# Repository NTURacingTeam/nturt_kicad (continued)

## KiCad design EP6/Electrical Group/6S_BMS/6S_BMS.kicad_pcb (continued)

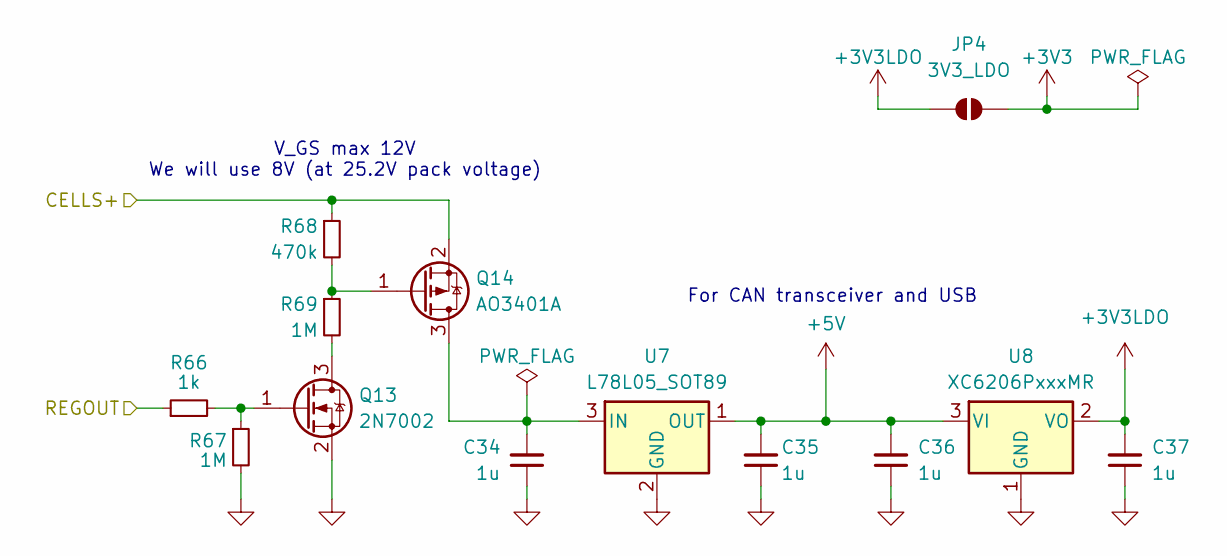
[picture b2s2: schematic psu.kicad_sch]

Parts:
C34, C35, C36, C37: 1u; C_0402_1005Metric
JP4: 3V3_LDO; SolderJumper-2_P1.3mm_Open_TrianglePad1.0x1.5mm
Q13: 2N7002; SOT-23
Q14: AO3401A; SOT-23
R66: 1k; R_0402_1005Metric
R67, R69: 1M; R_0402_1005Metric
R68: 470k; R_0402_1005Metric
U7: L78L05_SOT89; SOT-89-3
U8: XC6206PxxxMR; SOT-23-3

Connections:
+3V3: JP4.1 (A); also elsewhere on the board
+3V3LDO: C37.2, JP4.2 (B), U8.2 (VO)
+5V: C35.2, C36.2, U7.1 (OUT), U8.3 (VI); also elsewhere on the board
/CELLS+: Q14.2 (S), R68.1; also elsewhere on the board
/REGOUT: R66.1; also elsewhere on the board
GND: C34.1, C35.1, C36.1, C37.1, Q13.2 (S), R67.2, U7.2 (GND), U8.1 (GND); also elsewhere on the board
unnamed: Q13.3 (D), R69.2
unnamed: Q13.1 (G), R66.2, R67.1
unnamed: C34.2, Q14.3 (D), U7.3 (IN)
unnamed: Q14.1 (G), R68.2, R69.1

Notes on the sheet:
For CAN transceiver and USB
V_GS max 12V We will use 8V (at 25.2V pack voltage)

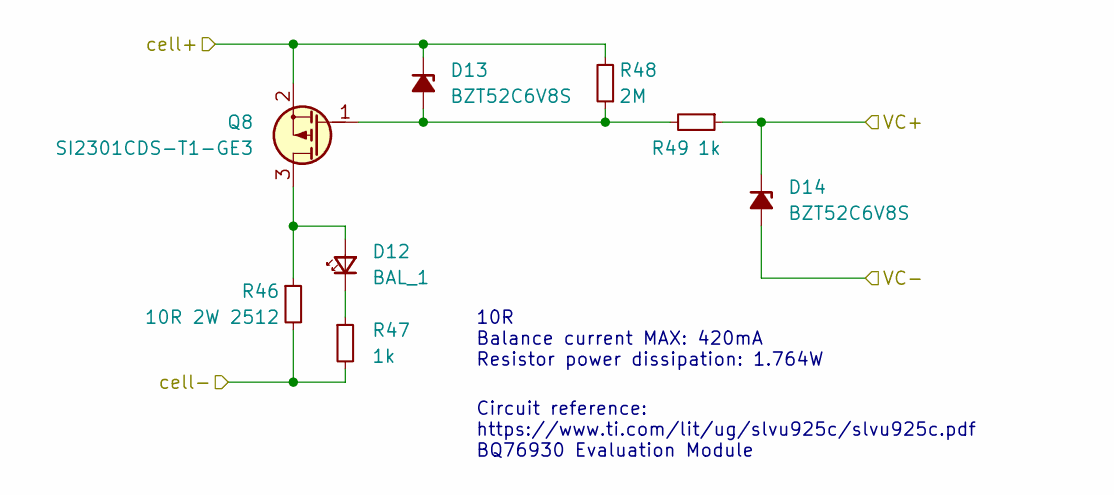
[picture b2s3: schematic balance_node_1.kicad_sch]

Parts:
D12: BAL_1; LED_0603_1608Metric
D13, D14: BZT52C6V8S; D_SOD-323
Q8: SI2301CDS-T1-GE3; SOT-23
R46: 10R 2W 2512; R_2512_6332Metric
R47, R49: 1k; R_0402_1005Metric
R48: 2M; R_0402_1005Metric

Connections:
/Balance Node 1/cell-: D13.1 (K), Q8.2 (S), R48.2; also elsewhere on the board
/C4: D14.2 (A); also elsewhere on the board
/C5: D14.1 (K), R49.1; also elsewhere on the board
unnamed: D12.1 (K), R47.1
unnamed: D13.2 (A), Q8.1 (G), R48.1, R49.2

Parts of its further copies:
D9, D15, D18, D21, D24: BAL_1; LED_0603_1608Metric
D10, D11, D16, D17, D19, D20, D22, D23, D25, D26: BZT52C6V8S; D_SOD-323
Q7, Q9, Q10, Q11, Q12: SI2301CDS-T1-GE3; SOT-23
R42, R50, R54, R58, R62: 10R 2W 2512; R_2512_6332Metric
R43, R51, R53, R55, R57, R59, R61, R63, R65: 1k; R_0402_1005Metric
R44, R52, R56, R60, R64: 2M; R_0402_1005Metric

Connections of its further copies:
/Balance Node 1/cell+: D10.1 (K), Q7.2 (S), R44.2; also elsewhere on the board
/Balance Node 1/cell-: R42.2, R43.2; also elsewhere on the board
/Balance Node 4/cell-: D22.1 (K), Q11.2 (S), R54.2, R55.2, R60.2; also elsewhere on the board
/Balance Node 5/cell-: D25.1 (K), Q12.2 (S), R58.2, R59.2, R64.2; also elsewhere on the board
/C0: D26.2 (A); also elsewhere on the board
/C1: D23.2 (A), D26.1 (K), R65.1; also elsewhere on the board
/C2: D20.2 (A), D23.1 (K), R61.1; also elsewhere on the board
/C3: D20.1 (K), R57.1; also elsewhere on the board
/C3.5: D17.2 (A); also elsewhere on the board
/C4: D17.1 (K), R53.1; also elsewhere on the board
/C5: D11.2 (A); also elsewhere on the board
/CT3: D19.1 (K), Q10.2 (S), R50.2, R51.2, R56.2; also elsewhere on the board
CELL-: R62.2, R63.2; also elsewhere on the board
unnamed: D9.2 (A), Q7.3 (D), R42.1
unnamed: D9.1 (K), R43.1
unnamed: D15.2 (A), Q9.3 (D), R50.1
unnamed: D15.1 (K), R51.1
unnamed: D16.2 (A), Q9.1 (G), R52.1, R53.2
unnamed: D18.2 (A), Q10.3 (D), R54.1
unnamed: D18.1 (K), R55.1
unnamed: D19.2 (A), Q10.1 (G), R56.1, R57.2
unnamed: D21.2 (A), Q11.3 (D), R58.1
unnamed: D21.1 (K), R59.1
unnamed: D22.2 (A), Q11.1 (G), R60.1, R61.2
unnamed: D24.2 (A), Q12.3 (D), R62.1
unnamed: D24.1 (K), R63.1
unnamed: D25.2 (A), Q12.1 (G), R64.1, R65.2

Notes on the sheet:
10R Balance current MAX: 420mA Resistor power dissipation: 1.764W
Circuit reference: https://www.ti.com/lit/ug/slvu925c/slvu925c.pdf BQ76930 Evaluation Module

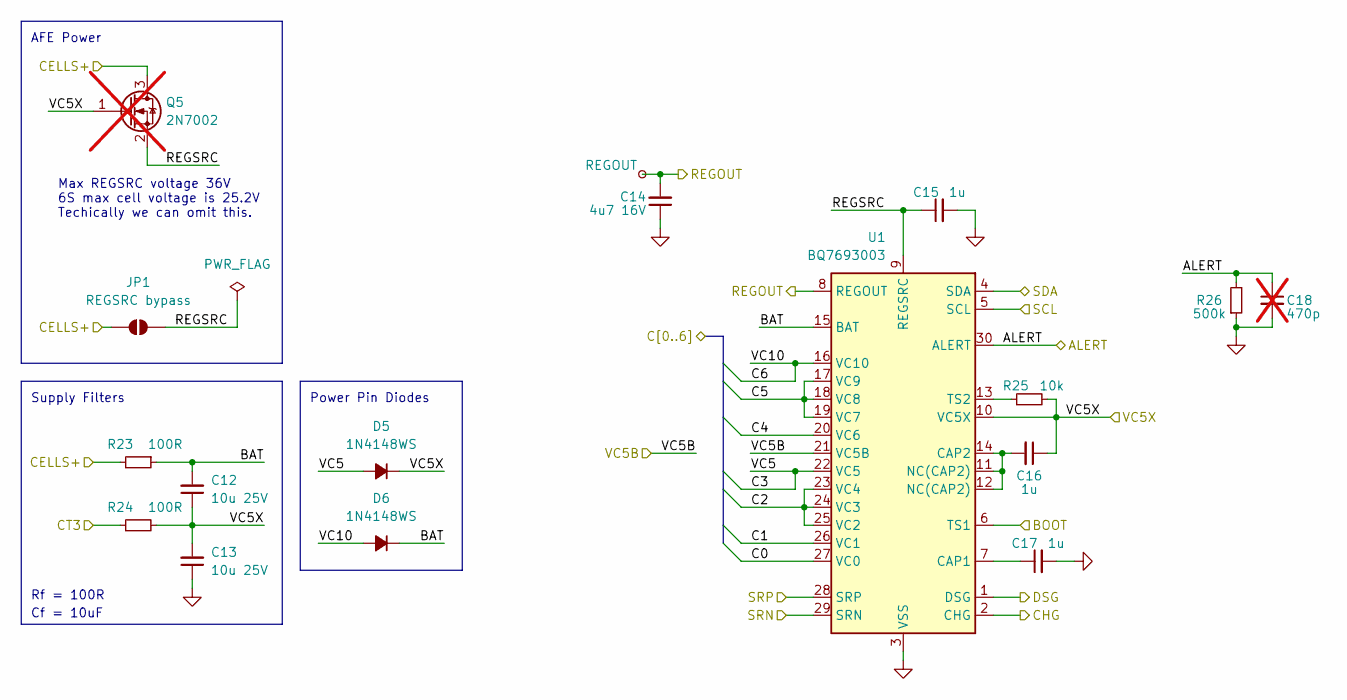
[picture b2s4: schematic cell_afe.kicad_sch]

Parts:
C12, C13: 10u 25V; C_0805_2012Metric
C14: 4u7 16V; C_0603_1608Metric
C15: 1u; C_0603_1608Metric
C16, C17: 1u; C_0402_1005Metric
C18: 470p; C_0402_1005Metric; not fitted
D5, D6: 1N4148WS; D_SOD-323
JP1: REGSRC bypass; SolderJumper-2_P1.3mm_Open_TrianglePad1.0x1.5mm
Q5: 2N7002; SOT-23; not fitted
R23, R24: 100R; R_0402_1005Metric
R25: 10k; R_0402_1005Metric
R26: 500k; R_0402_1005Metric
TP12: REGOUT; TestPoint_Pad_D1.0mm
U1: BQ7693003; TSSOP-30_4.4x7.8mm_P0.5mm

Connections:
/AFE/BAT: C12.2, D6.1 (K), R23.1, U1.15 (BAT)
/AFE/REGSRC: C15.1, JP1.1 (A), Q5.2 (S), U1.9 (REGSRC)
/ALERT: C18.1, R26.2, U1.30 (ALERT); also elsewhere on the board
/C0: U1.27 (VC0); also elsewhere on the board
/C1: U1.26 (VC1); also elsewhere on the board
/C2: U1.23 (VC4), U1.24 (VC3), U1.25 (VC2); also elsewhere on the board
/C3: D5.2 (A), U1.22 (VC5); also elsewhere on the board
/C3.5: U1.21 (VC5B); also elsewhere on the board
/C4: U1.20 (VC6); also elsewhere on the board
/C5: U1.17 (VC9), U1.18 (VC8), U1.19 (VC7); also elsewhere on the board
/CELLS+: JP1.2 (B), Q5.3 (D), R23.2; also elsewhere on the board
/CHG_EN: U1.2 (CHG); also elsewhere on the board
/CT3: R24.1; also elsewhere on the board
/DSC_EN: U1.1 (DSG); also elsewhere on the board
/MODE_CTL: U1.6 (TS1); also elsewhere on the board
/REGOUT: C14.2, TP12.1, U1.8 (REGOUT); also elsewhere on the board
/SCL: U1.5 (SCL); also elsewhere on the board
/SDA: U1.4 (SDA); also elsewhere on the board
/SRN: U1.29 (SRN); also elsewhere on the board
/SRP: U1.28 (SRP); also elsewhere on the board
/VC5X: C12.1, C13.2, C16.1, D5.1 (K), Q5.1 (G), R24.2, R25.2, U1.10 (VC5X); also elsewhere on the board
GND: C13.1, C14.1, C15.2, C17.2, C18.2, R26.1, U1.3 (VSS); also elsewhere on the board
unnamed: C17.1, U1.7 (CAP1)
unnamed: C16.2, U1.11 (NC(CAP2)), U1.12 (NC(CAP2)), U1.14 (CAP2)
unnamed: R25.1, U1.13 (TS2)

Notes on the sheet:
Max REGSRC voltage 36V 6S max cell voltage is 25.2V Techically we can omit this.
AFE Power
Cf = 10uF
Power Pin Diodes
Supply Filters
Rf = 100R

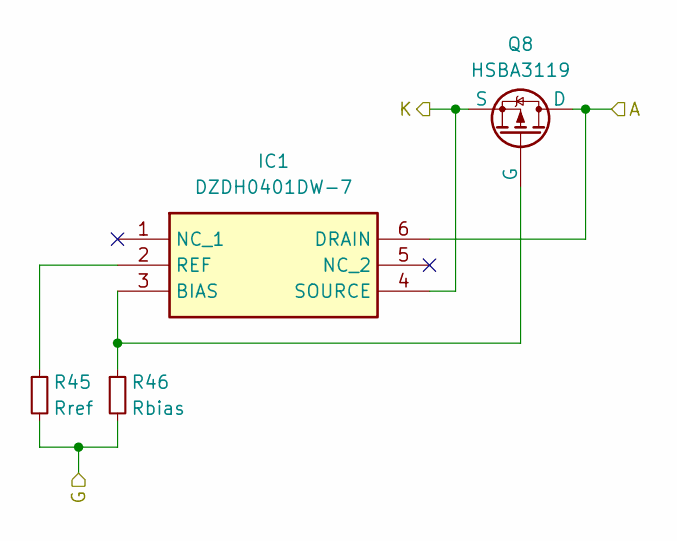
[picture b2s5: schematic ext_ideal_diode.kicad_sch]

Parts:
IC1: DZDH0401DW-7; SOT65P210X110-6N; Mouser Part Number 621-DZDH0401DW-7
Q8: HSBA3119; HSBA3119_PRPAK5X6
R45: Rref; R_0402_1005Metric
R46: Rbias; R_0402_1005Metric

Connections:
/EXT Ideal Diode/A: IC1.6 (DRAIN), Q8.D; also elsewhere on the board
/PACK+: IC1.4 (SOURCE), Q8.S; also elsewhere on the board

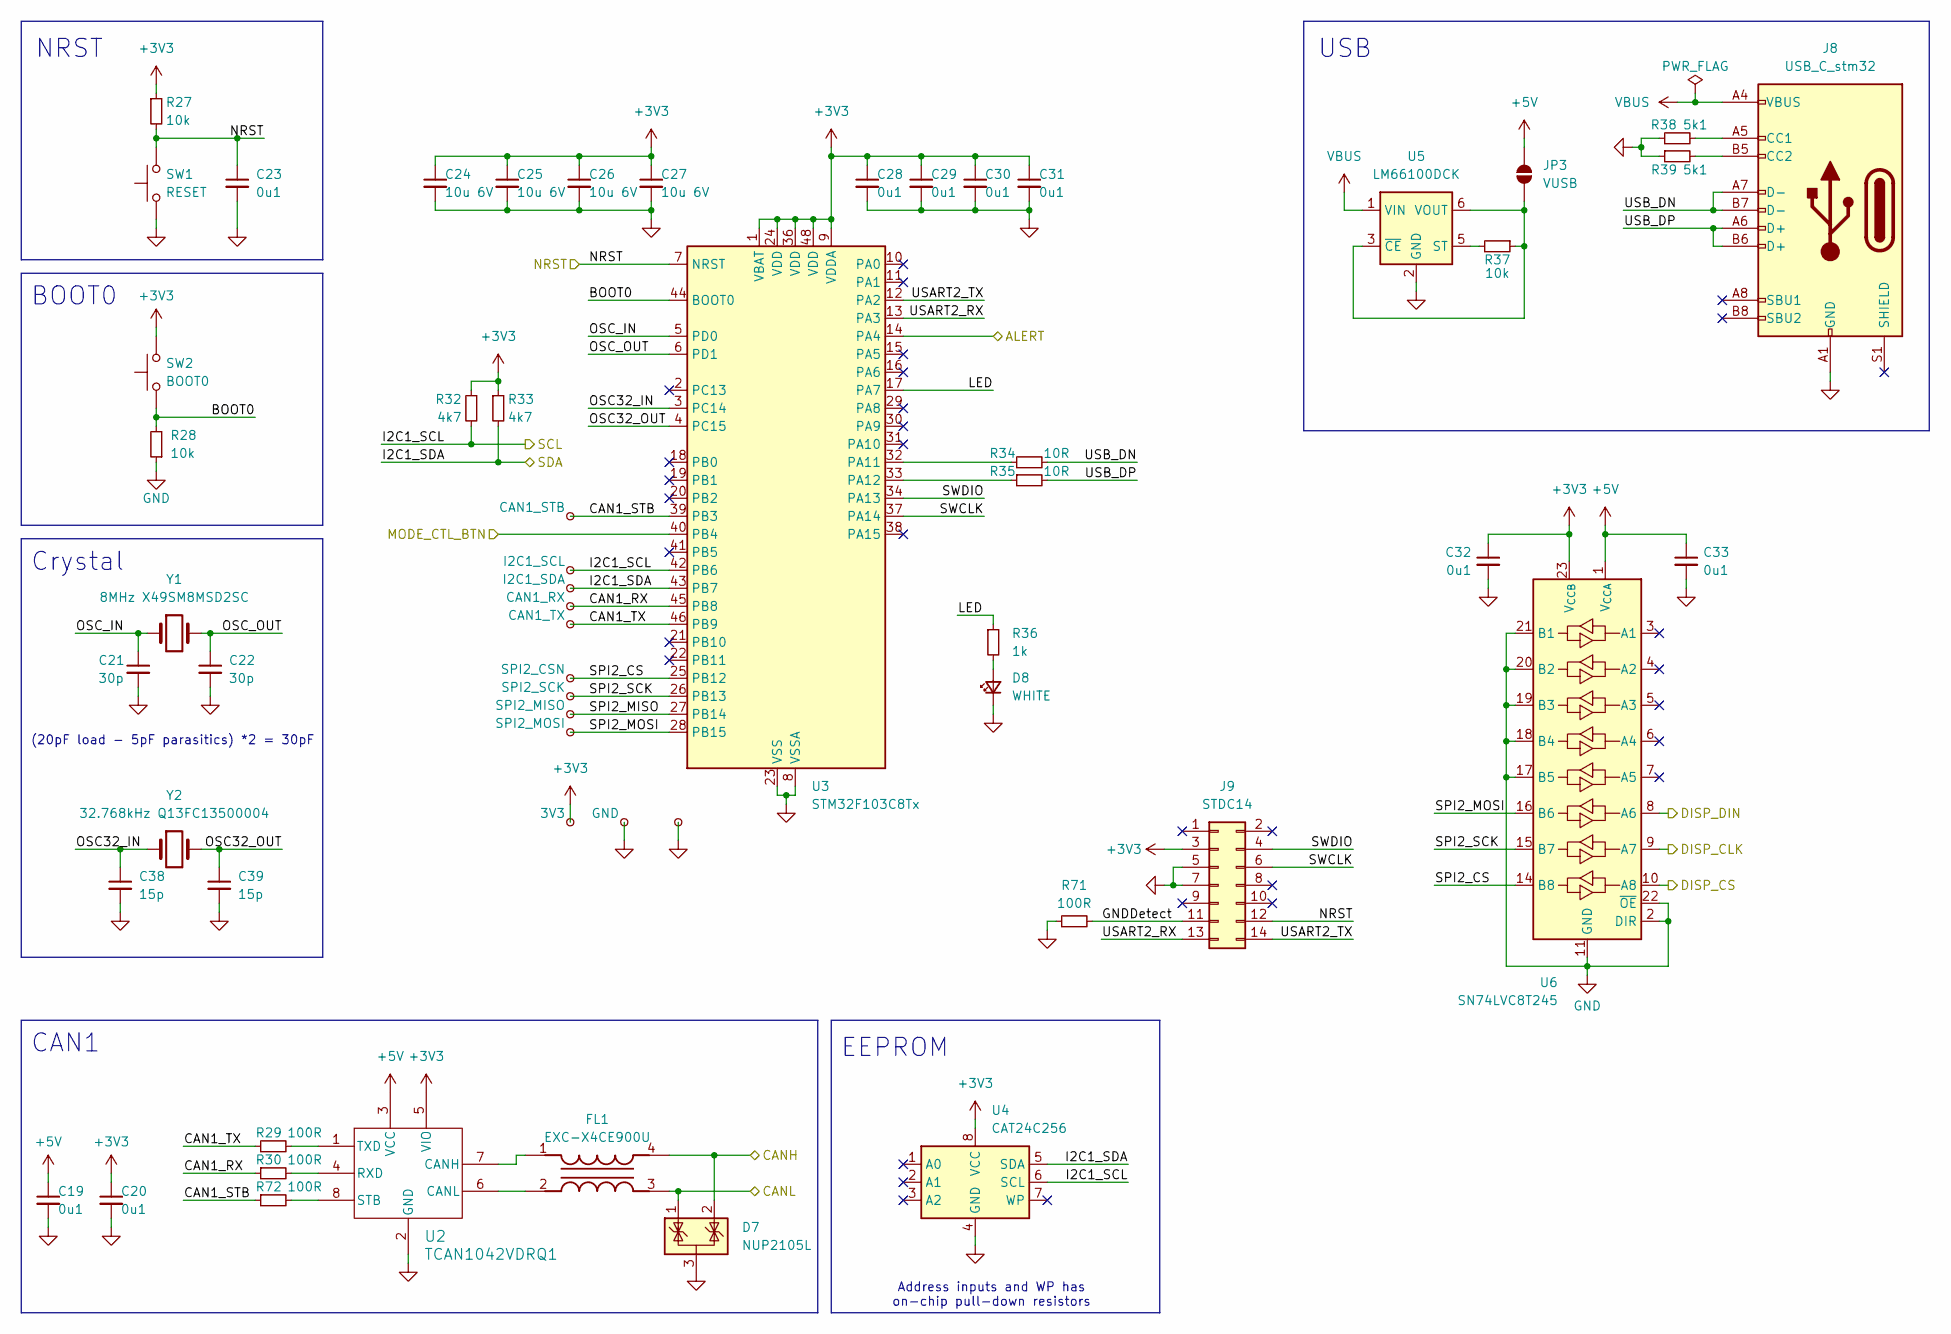
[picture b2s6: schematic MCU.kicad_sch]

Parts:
C19, C20, C23, C28, C29, C30, C31, C32, C33: 0u1; C_0402_1005Metric
C21, C22: 30p; C_0402_1005Metric
C24, C25, C26, C27: 10u 6V; C_0402_1005Metric
C38, C39: 15p; C_0402_1005Metric
D7: NUP2105L; SOT-23
D8: WHITE; LED_0603_1608Metric
FL1: EXC-X4CE900U; EXCX4CE900U; Mouser Part Number 667-EXC-X4CE900U
J8: USB_C_stm32; USB_C_Receptacle_GCT_USB4105-xx-A_16P_TopMnt_Horizontal
J9: STDC14; box_header_14P_pitch127
JP3: VUSB; SolderJumper-2_P1.3mm_Open_TrianglePad1.0x1.5mm
R27, R28, R37: 10k; R_0402_1005Metric
R29, R30, R72: 100R; R_0402_1005Metric
R32, R33: 4k7; R_0402_1005Metric
R34, R35: 10R; R_0402_1005Metric
R36: 1k; R_0603_1608Metric
R38, R39: 5k1; R_0402_1005Metric
R71: 100R; R_0603_1608Metric
SW1: RESET; SW_Tactile_SPST_NO_Straight_CK_PTS636Sx25SMTRLFS
SW2: BOOT0; SW_Tactile_SPST_NO_Straight_CK_PTS636Sx25SMTRLFS
TP1: I2C1_SCL; TestPoint_Pad_D1.0mm
TP2: I2C1_SDA; TestPoint_Pad_D1.0mm
TP3: CAN1_RX; TestPoint_Pad_D1.0mm
TP4: CAN1_TX; TestPoint_Pad_D1.0mm
TP5: CAN1_STB; TestPoint_Pad_D1.0mm
TP6: SPI2_CSN; TestPoint_Pad_D1.0mm
TP7: SPI2_SCK; TestPoint_Pad_D1.0mm
TP8: SPI2_MISO; TestPoint_Pad_D1.0mm
TP9: SPI2_MOSI; TestPoint_Pad_D1.0mm
TP10: 3V3; TestPoint_Pad_D1.0mm
TP11, TP14: GND; TestPoint_Pad_D1.0mm
U2: TCAN1042VDRQ1; SOIC-8_3.9x4.9mm_P1.27mm
U3: STM32F103C8Tx; LQFP-48_7x7mm_P0.5mm
U4: CAT24C256; SOIC-8_3.9x4.9mm_P1.27mm
U5: LM66100DCK; SOT-363_SC-70-6
U6: SN74LVC8T245; TSSOP-24_4.4x7.8mm_P0.65mm
Y1: 8MHz X49SM8MSD2SC; Crystal_SMD_5032-2Pin_5.0x3.2mm
Y2: 32.768kHz Q13FC13500004; Crystal_SMD_3215-2Pin_3.2x1.5mm

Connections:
+3V3: C20.1, C24.1, C25.1, C26.1, C27.1, C28.1, C29.1, C30.1, C31.1, C32.1, J9.3, R27.1, R32.1, R33.1, SW2.2, TP10.1, U2.5 (VIO), U3.1 (VBAT), U3.9 (VDDA), U3.24 (VDD), U3.36 (VDD), U3.48 (VDD), U4.8 (VCC), U6.23 (V_{CCB}), U6.24 (V_{CCB}); also elsewhere on the board
+5V: C19.1, C33.1, JP3.2 (B), U2.3 (VCC), U6.1 (V_{CCA}); also elsewhere on the board
/ALERT: U3.14 (PA4); also elsewhere on the board
/CANH: D7.2 (K), FL1.4; also elsewhere on the board
/CANL: D7.1 (K), FL1.3; also elsewhere on the board
/DISP_CLK: U6.9 (A7); also elsewhere on the board
/DISP_CS: U6.10 (A8); also elsewhere on the board
/DISP_DIN: U6.8 (A6); also elsewhere on the board
/MCU/BOOT0: R28.2, SW2.1, U3.44 (BOOT0)
/MCU/CAN1_RX: R30.1, TP3.1, U3.45 (PB8)
/MCU/CAN1_STB: R72.1, TP5.1, U3.39 (PB3)
/MCU/CAN1_TX: R29.1, TP4.1, U3.46 (PB9)
/MCU/GNDDetect: J9.11, R71.2
/MCU/LED: R36.1, U3.17 (PA7)
/MCU/OSC32_IN: C38.1, U3.3 (PC14), Y2.1
/MCU/OSC32_OUT: C39.1, U3.4 (PC15), Y2.2
/MCU/OSC_IN: C21.1, U3.5 (PD0), Y1.1
/MCU/OSC_OUT: C22.1, U3.6 (PD1), Y1.2
/MCU/SPI2_CS: TP6.1, U3.25 (PB12), U6.14 (B8)
/MCU/SPI2_MISO: TP8.1, U3.27 (PB14)
/MCU/SPI2_MOSI: TP9.1, U3.28 (PB15), U6.16 (B6)
/MCU/SPI2_SCK: TP7.1, U3.26 (PB13), U6.15 (B7)
/MCU/SWCLK: J9.6, U3.37 (PA14)
/MCU/SWDIO: J9.4, U3.34 (PA13)
/MCU/USART2_RX: J9.13, U3.13 (PA3)
/MCU/USART2_TX: J9.14, U3.12 (PA2)
/MCU/USB_DN: J8.A7 (D-), J8.B7 (D-), R34.2
/MCU/USB_DP: J8.A6 (D+), J8.B6 (D+), R35.2
/MCU_RST: C23.1, J9.12, R27.2, SW1.2, U3.7 (NRST); also elsewhere on the board
/MODE_CTL: U3.40 (PB4); also elsewhere on the board
/SCL: R32.2, TP1.1, U3.42 (PB6), U4.6 (SCL); also elsewhere on the board
/SDA: R33.2, TP2.1, U3.43 (PB7), U4.5 (SDA); also elsewhere on the board
GND: C19.2, C20.2, C21.2, C22.2, C23.2, C24.2, C25.2, C26.2, C27.2, C28.2, C29.2, C30.2, C31.2, C32.2, C33.2, C38.2, C39.2, D7.3 (A), D8.1 (K), J8.A1 (GND), J8.A12 (GND), J8.B1 (GND), J8.B12 (GND), J9.5, J9.7, R28.1, R38.1, R39.1, R71.1, SW1.1, TP11.1, TP14.1, U2.2 (GND), U3.8 (VSSA), U3.23 (VSS), U3.35 (VSS), U3.47 (VSS), U4.4 (GND), U5.2 (GND), U6.2 (DIR), U6.11 (GND), U6.12 (GND), U6.13 (GND), U6.17 (B5), U6.18 (B4), U6.19 (B3), U6.20 (B2), U6.21 (B1), U6.22 (~OE); also elsewhere on the board
unnamed: D8.2 (A), R36.2
unnamed: J8.A5 (CC1), R38.2
unnamed: J8.B5 (CC2), R39.2
unnamed: JP3.1 (A), R37.1, U5.3 (~CE), U5.6 (VOUT)
unnamed: FL1.1, U2.7 (CANH)
unnamed: FL1.2, U2.6 (CANL)
unnamed: R30.2, U2.4 (RXD)
unnamed: R72.2, U2.8 (STB)
unnamed: R29.2, U2.1 (TXD)
unnamed: R34.1, U3.32 (PA11)
unnamed: R35.1, U3.33 (PA12)
unnamed: R37.2, U5.5 (ST)
VBUS: J8.A4 (VBUS), J8.A9 (VBUS), J8.B4 (VBUS), J8.B9 (VBUS), U5.1 (VIN)

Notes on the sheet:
Address inputs and WP has on-chip pull-down resistors
BOOT0
CAN1
(20pF load - 5pF parasitics) *2 = 30pF
USB
NRST
Crystal
EEPROM

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
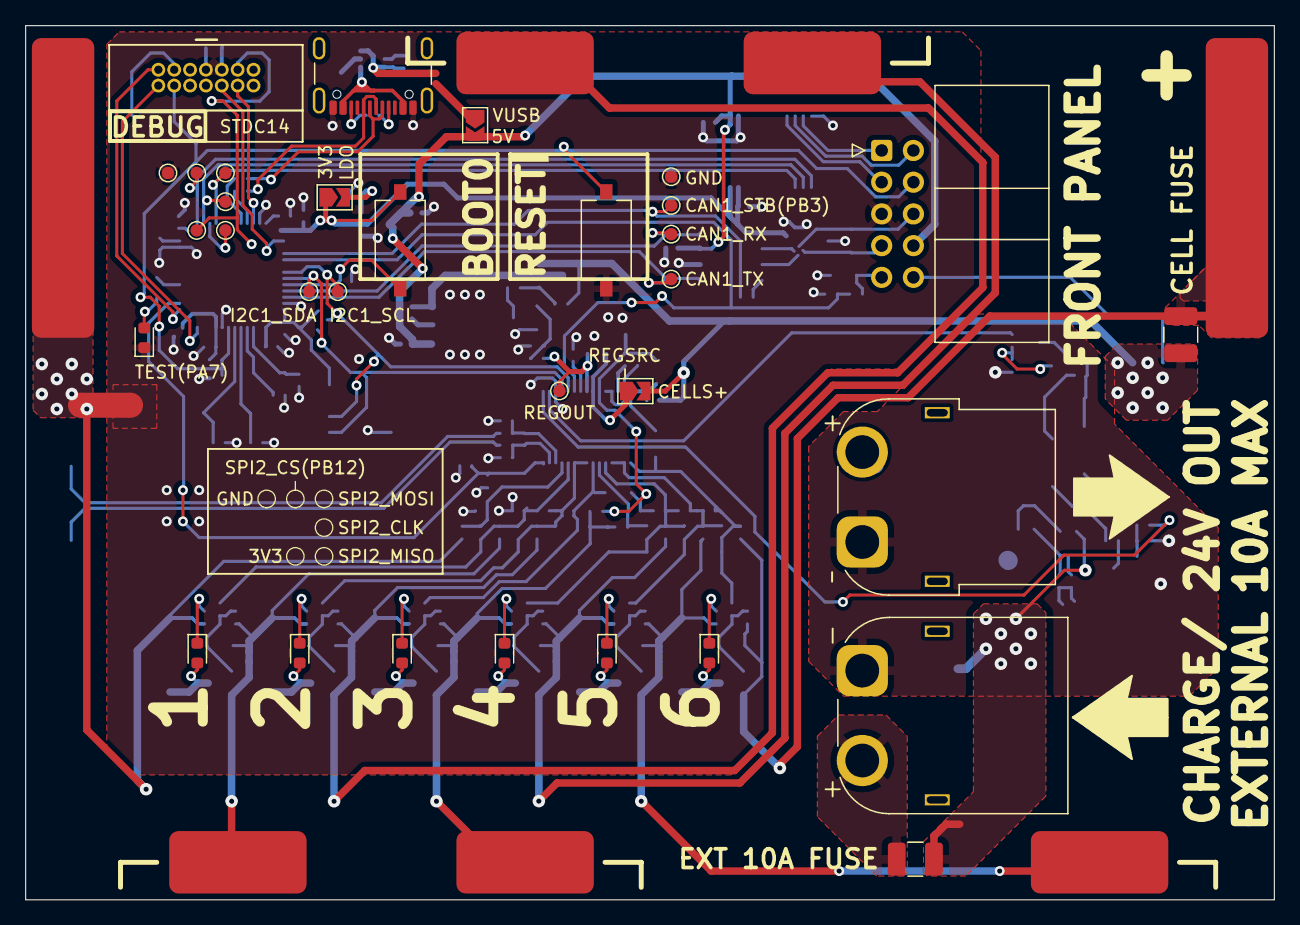
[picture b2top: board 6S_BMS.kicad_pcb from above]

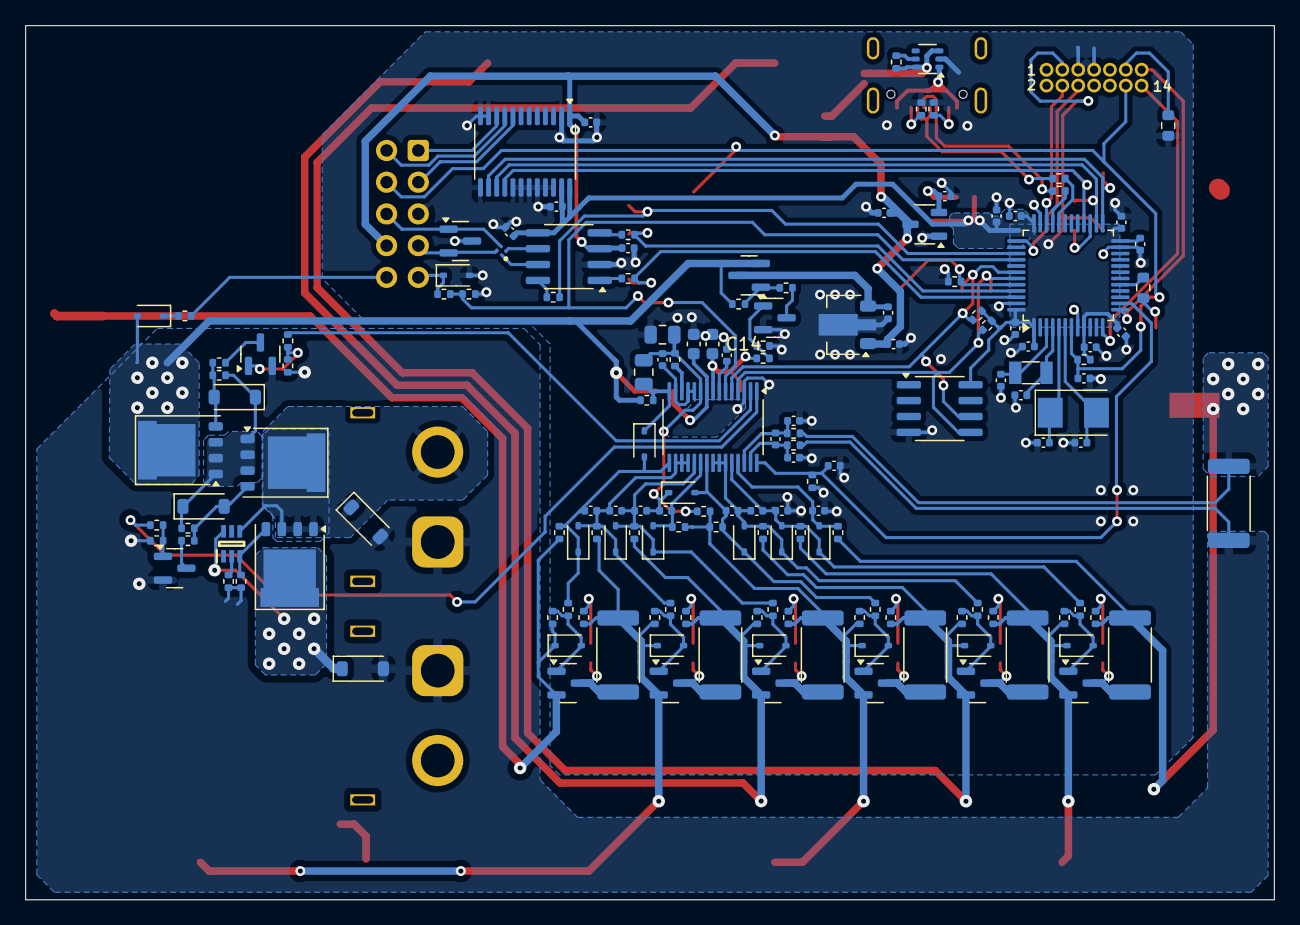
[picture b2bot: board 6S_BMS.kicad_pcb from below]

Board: 2 copper layers, 100.0 x 70.0 mm, 189 parts (155 on the bottom side), 112 nets.

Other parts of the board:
NT1: NetTie_2; NetTie-2_SMD_Pad2.0mm
Q6: HSBA3119; HSBA3119_PRPAK5X6
R40: Rref; R_0402_1005Metric
R41: Rbias; R_0402_1005Metric

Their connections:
/EXT Ideal Diode/A: Q6.D; also elsewhere on the board
/PACK+: Q6.S; also elsewhere on the board
/PACK-: R40.2, R41.2; also elsewhere on the board
CELL-: NT1.2; also elsewhere on the board
GND: NT1.1; also elsewhere on the board

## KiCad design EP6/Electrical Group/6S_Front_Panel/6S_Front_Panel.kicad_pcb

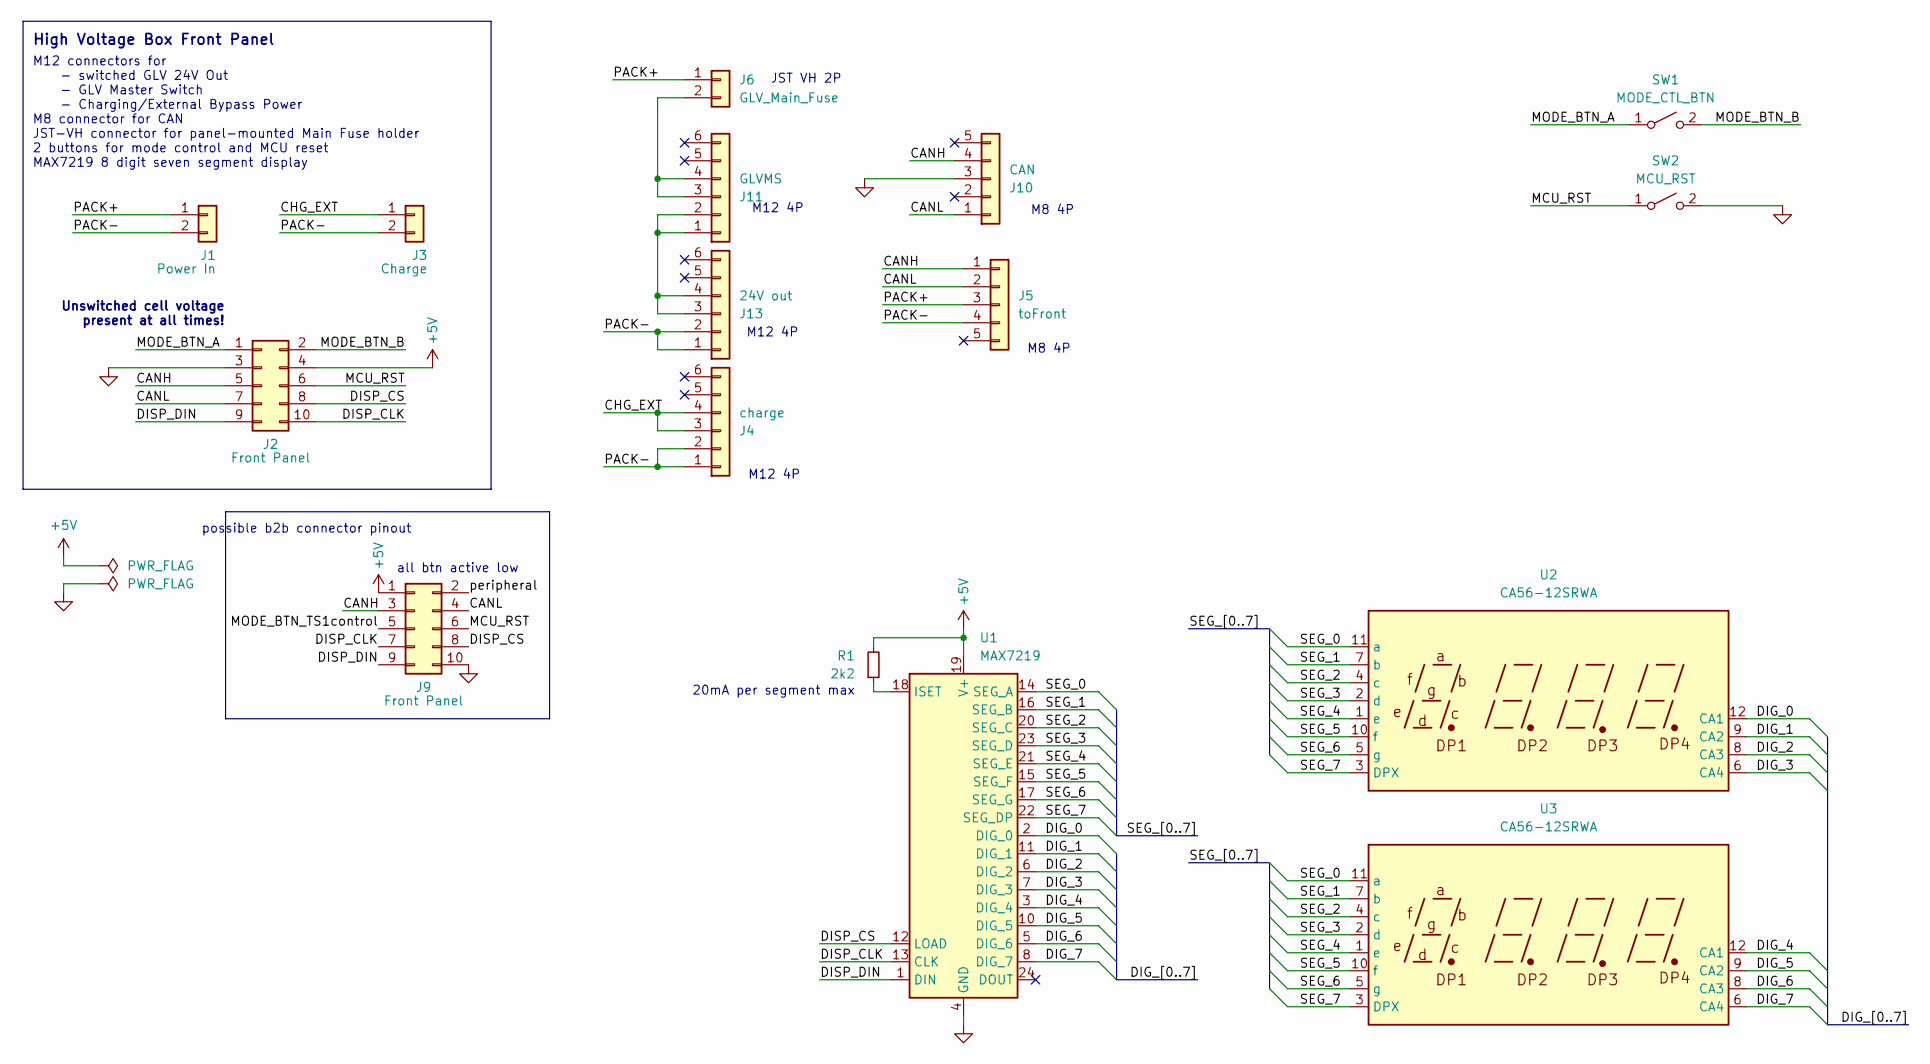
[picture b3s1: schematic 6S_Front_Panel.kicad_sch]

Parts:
J1: Power In; AMASS_XT60PW-M_1x02_P7.20mm_Horizontal
J2, J9: Front Panel; IDC-Header_2x05_P2.54mm_Horizontal
J3: Charge; AMASS_XT60PW-F_1x02_P7.20mm_Horizontal
J4: charge; M12-5P-ground; Part Number 1-0601FBV0T
J5: toFront; WP-04F3-26-11
J6: GLV_Main_Fuse; JST_VH_B2PS-VH_1x02_P3.96mm_Horizontal
J10: CAN; WP-04F3-26-11
J11: GLVMS; M12-5P-ground; Part Number 1-0601FBV0T
J13: 24V out; M12-5P-ground; Part Number 1-0601FBV0T
R1: 2k2; R_0402_1005Metric_Pad0.72x0.64mm_HandSolder
SW1: MODE_CTL_BTN; PinHeader_1x02_P2.54mm_Vertical
SW2: MCU_RST; PinHeader_1x02_P2.54mm_Vertical
U1: MAX7219; SOIC-24W_7.5x15.4mm_P1.27mm
U2, U3: CA56-12SRWA; CA56-12EWA

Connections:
+5V: J2.4, J9.1, R1.2, U1.19 (V+)
/CANH: J2.5, J5.1, J9.3, J10.4
/CANL: J2.7, J5.2, J9.4, J10.1
/CHG_EXT: J3.1, J4.3, J4.4
/DIG_0: U1.2 (DIG_0), U2.12 (CA1)
/DIG_1: U1.11 (DIG_1), U2.9 (CA2)
/DIG_2: U1.6 (DIG_2), U2.8 (CA3)
/DIG_3: U1.7 (DIG_3), U2.6 (CA4)
/DIG_4: U1.3 (DIG_4), U3.12 (CA1)
/DIG_5: U1.10 (DIG_5), U3.9 (CA2)
/DIG_6: U1.5 (DIG_6), U3.8 (CA3)
/DIG_7: U1.8 (DIG_7), U3.6 (CA4)
/DISP_CLK: J2.10, J9.7, U1.13 (CLK)
/DISP_CS: J2.8, J9.8, U1.12 (LOAD)
/DISP_DIN: J2.9, J9.9, U1.1 (DIN)
/MCU_RST: J2.6, J9.6, SW2.1 (A)
/MODE_BTN_A: J2.1, SW1.1 (A)
/MODE_BTN_B: J2.2, SW1.2 (B)
/MODE_BTN_TS1control: J9.5
/PACK+: J1.1, J5.3, J6.1
/PACK-: J1.2, J3.2, J4.1, J4.2, J5.4, J13.1, J13.2
/SEG_0: U1.14 (SEG_A), U2.11 (a), U3.11 (a)
/SEG_1: U1.16 (SEG_B), U2.7 (b), U3.7 (b)
/SEG_2: U1.20 (SEG_C), U2.4 (c), U3.4 (c)
/SEG_3: U1.23 (SEG_D), U2.2 (d), U3.2 (d)
/SEG_4: U1.21 (SEG_E), U2.1 (e), U3.1 (e)
/SEG_5: U1.15 (SEG_F), U2.10 (f), U3.10 (f)
/SEG_6: U1.17 (SEG_G), U2.5 (g), U3.5 (g)
/SEG_7: U1.22 (SEG_DP), U2.3 (DPX), U3.3 (DPX)
/peripheral: J9.2
GND: J2.3, J9.10, J10.3, SW2.2 (B), U1.4 (GND), U1.9 (GND)
unnamed: J11.1, J11.2, J13.3, J13.4
unnamed: J6.2, J11.3, J11.4
unnamed: R1.1, U1.18 (ISET)

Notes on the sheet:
JST VH 2P
M8 4P
M12 4P
20mA per segment max
High Voltage Box Front Panel
possible b2b connector pinout
M12 connectors for - switched GLV 24V Out - GLV Master Switch - Charging/External Bypass Power M8 connector for CAN JST-VH connector for panel-mounted Main Fuse holder 2 buttons for mode control and MCU reset MAX7219 8 digit seven segment display
Unswitched cell voltage present at all times!
all btn active low

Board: 2 copper layers, 16 parts (5 on the bottom side), 32 nets, no tracks yet.

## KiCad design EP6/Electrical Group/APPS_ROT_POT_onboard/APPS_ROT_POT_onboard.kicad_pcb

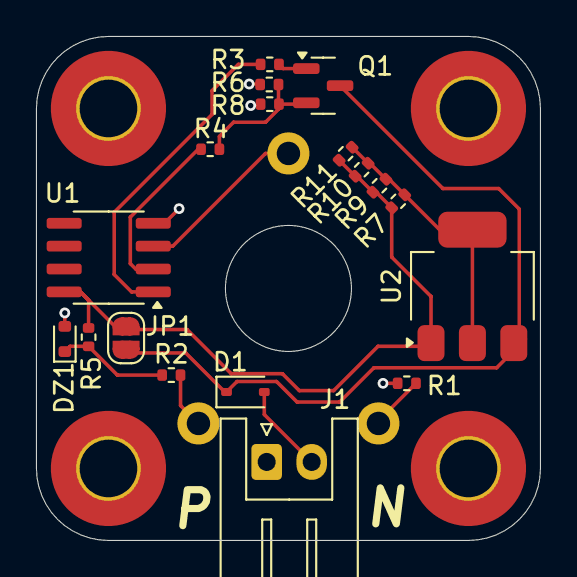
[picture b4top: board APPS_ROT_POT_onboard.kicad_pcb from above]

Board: 2 copper layers, 28.0 x 28.0 mm, 23 parts (1 on the bottom side), 13 nets.

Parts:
D1: 1N4148; D_SOD-323
DZ1: 5.6V; D_SOD-523
H1, H2, H3, H4: MountingHole_Pad; MountingHole_3.2mm_M3_Pad_TopBottom
J1: current; JST_XH_S2B-XH-A_1x02_P2.50mm_Horizontal
JP1: SolderJumper_2_Open; SolderJumper-2_P1.3mm_Open_RoundedPad1.0x1.5mm
Q1: 2N7002; SOT-23
R1, R2, R5: 1k; R_0402_1005Metric
R3, R4: 10k; R_0402_1005Metric
R6, R8: 510R; R_0402_1005Metric
R7, R9, R10, R11: 3k3; R_0402_1005Metric
RV1: 100k PTN15-E100DB10-H; Potentiometer_Piher_PT-15-V15_Vertical_Hole
U1: LM358; SOIC-8_3.9x4.9mm_P1.27mm
U2: AMS1117-3.3; SOT-223-3_TabPin2

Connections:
GND: DZ1.2 (A), J1.1, R1.2, R6.1, R8.1, U1.4 (V-)
unnamed: D1.2 (A), J1.2
unnamed: DZ1.1 (K), R2.1, R5.2
unnamed: JP1.1 (A), R5.1, R7.2, R9.2, R10.2, R11.2, U1.8 (V+), U2.1 (GND)
unnamed: Q1.1 (G), R3.2
unnamed: Q1.2 (S), R4.2, R6.2, R8.2
unnamed: R1.1, RV1.3
unnamed: R2.2, RV1.1
unnamed: R3.1, U1.1
unnamed: RV1.2, U1.3 (+)
unnamed: R4.1, U1.2 (-)
unnamed: R7.1, R9.1, R10.1, R11.1, U2.2 (VO)
VCC: D1.1 (K), JP1.2 (B), Q1.3 (D), U2.3 (VI)

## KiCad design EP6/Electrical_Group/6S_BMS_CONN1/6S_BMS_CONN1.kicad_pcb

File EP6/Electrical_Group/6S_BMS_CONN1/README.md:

# 6S_BMS_CONN1 KiCad Project

## Project Overview
This repository contains the KiCad project for the **6S_BMS_CONN1** design, developed as part of the **Electrical Group**.

## Author
- **Name:** [Jack Kuo](https://github.com/chemmy-jack)
- **Team:** NTU Racing Team Electrical Group

## Revision History

| Version | Date       | Author       | Description                  |
|---------|------------|--------------|------------------------------|
| 1.0     | 2025-03-10 | [Jack Kuo](https://github.com/chemmy-jack)  | Initial project creation. (older version not documented)   |
| 1.1     | 2025-05-05 | [Jack Kuo](https://github.com/chemmy-jack)  | fix M12 L-coded hole too small mistake.  add fillet to board cut. change IDC to 6S_BMS V2.0 to 12pin (new design. 2 more button input and 1 more LED WS2812 output). add 5V ext and WS2812 connector.|

## To-Do List

## License
<!-- This project is licensed under [Your License]. See the LICENSE file for details. -->
none

## Contact
For questions or contributions, please contact [ntu.racing@gmail.com].

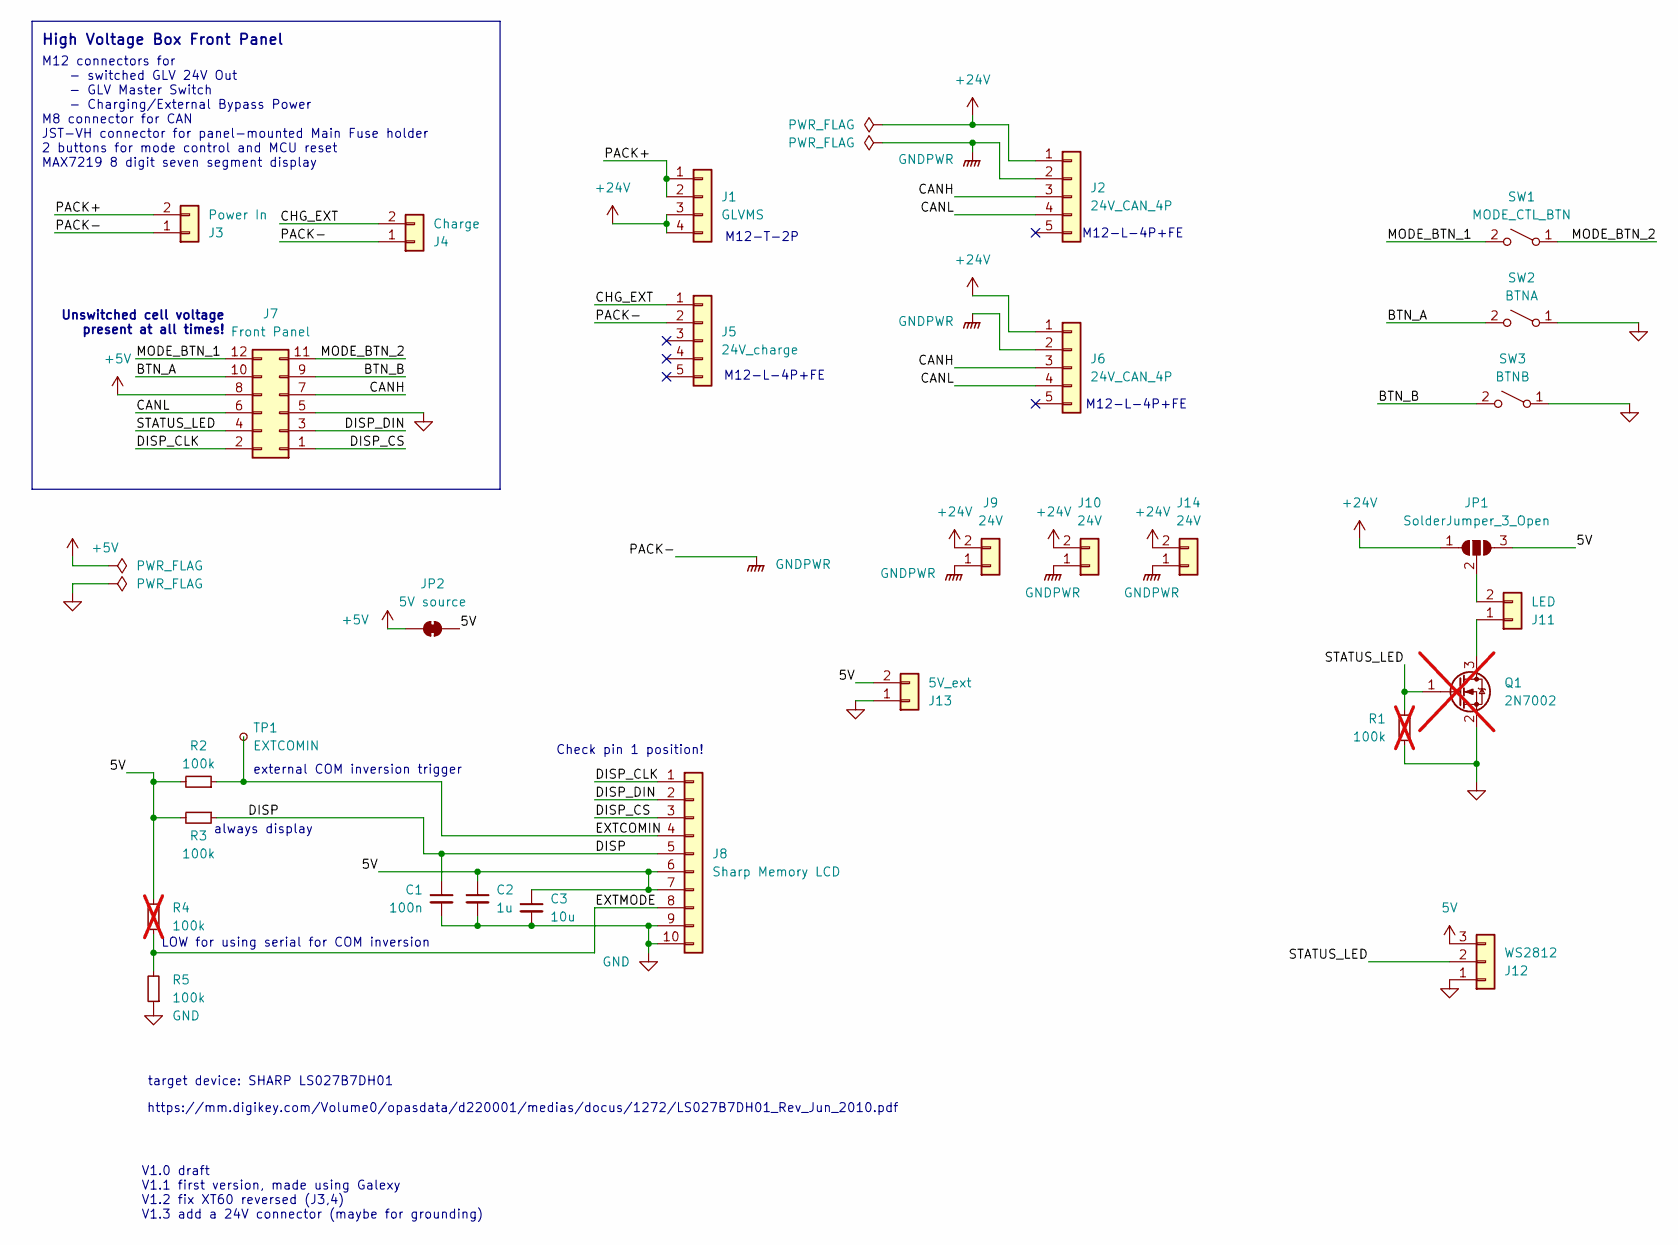
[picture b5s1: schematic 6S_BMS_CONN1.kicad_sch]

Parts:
C1: 100n; C_0603_1608Metric_Pad1.08x0.95mm_HandSolder
C2: 1u; C_0603_1608Metric_Pad1.08x0.95mm_HandSolder
C3: 10u; C_0603_1608Metric_Pad1.08x0.95mm_HandSolder
J1: GLVMS; NianYeong-M12-T-M4P
J2, J6: 24V_CAN_4P; NianYeong-M12-L-F5P
J3: Power In; AMASS_XT60PW-M_1x02_P7.20mm_Horizontal
J4: Charge; AMASS_XT60PW-F_1x02_P7.20mm_Horizontal
J5: 24V_charge; NianYeong-M12-L-F5P
J7: Front Panel; IDC-Header_2x06_P2.54mm_Horizontal
J8: Sharp Memory LCD; Hirose_FH12-10S-0.5SH_1x10-1MP_P0.50mm_Horizontal
J9, J10, J14: 24V; JST_VH_B2P-VH_1x02_P3.96mm_Vertical
J11: LED; JST_PH_S2B-PH-K_1x02_P2.00mm_Horizontal
J12: WS2812; JST_PH_B3B-PH-K_1x03_P2.00mm_Vertical
J13: 5V_ext; JST_XH_B2B-XH-A_1x02_P2.50mm_Vertical
JP1: SolderJumper_3_Open; SolderJumper-3_P1.3mm_Open_RoundedPad1.0x1.5mm
JP2: 5V source; SolderJumper-2_P1.3mm_Bridged2Bar_RoundedPad1.0x1.5mm
Q1: 2N7002; SOT-23; not fitted
R1, R4: 100k; R_0603_1608Metric; not fitted
R2, R3, R5: 100k; R_0603_1608Metric
SW1: MODE_CTL_BTN; JST_PH_S2B-PH-K_1x02_P2.00mm_Horizontal
SW2: BTNA; JST_PH_S2B-PH-K_1x02_P2.00mm_Horizontal
SW3: BTNB; JST_PH_S2B-PH-K_1x02_P2.00mm_Horizontal
TP1: EXTCOMIN; TestPoint_Pad_D1.0mm

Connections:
5V: C2.1, C3.1, J8.6, J8.7, J12.3, J13.2, JP1.3 (B), JP2.2 (B), R2.2, R3.2, R4.2
+5V: J7.8, JP2.1 (A)
+24V: J1.3, J1.4, J2.1, J6.1, J9.2, J10.2, J14.2, JP1.1 (A)
/BTN_A: J7.10, SW2.2 (B)
/BTN_B: J7.9, SW3.2 (B)
/CANH: J2.3, J6.3, J7.7
/CANL: J2.4, J6.4, J7.6
/CHG_EXT: J4.2, J5.1
/DISP: C1.1, J8.5, R3.1
/DISP_CLK: J7.2, J8.1
/DISP_CS: J7.1, J8.3
/DISP_DIN: J7.3, J8.2
/EXTCOMIN: J8.4, R2.1, TP1.1
/EXTMODE: J8.8, R4.1, R5.2
/MODE_BTN_1: J7.12, SW1.2 (B)
/MODE_BTN_2: J7.11, SW1.1 (A)
/PACK+: J1.1, J1.2, J3.2
/STATUS_LED: J7.4, J12.2, Q1.1 (G), R1.2
GND: C1.2, C2.2, C3.2, J7.5, J8.9, J8.10, J12.1, J13.1, Q1.2 (S), R1.1, R5.1, SW2.1 (A), SW3.1 (A)
GNDPWR: J2.2, J3.1, J4.1, J5.2, J6.2, J9.1, J10.1, J14.1
unnamed: J11.1, Q1.3 (D)
unnamed: J11.2, JP1.2 (C)

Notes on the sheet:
High Voltage Box Front Panel
Check pin 1 position!
always display
M12-L-4P+FE
LOW for using serial for COM inversion
V1.0 draft V1.1 first version, made using Galexy V1.2 fix XT60 reversed (J3,4) V1.3 add a 24V connector (maybe for grounding)
Unswitched cell voltage present at all times!
M12 connectors for - switched GLV 24V Out - GLV Master Switch - Charging/External Bypass Power M8 connector for CAN JST-VH connector for panel-mounted Main Fuse holder 2 buttons for mode control and MCU reset MAX7219 8 digit seven segment display
M12-T-2P
https://mm.digikey.com/Volume0/opasdata/d220001/medias/docus/1272/LS027B7DH01_Rev_Jun_2010.pdf
target device: SHARP LS027B7DH01
external COM inversion trigger
